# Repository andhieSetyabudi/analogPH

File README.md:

# analogPH
analogPH is a library to access my pH-board. Arduino compatibility. My pH using ADC-I2C ( ADS1112 ) for the main ADC-chip.

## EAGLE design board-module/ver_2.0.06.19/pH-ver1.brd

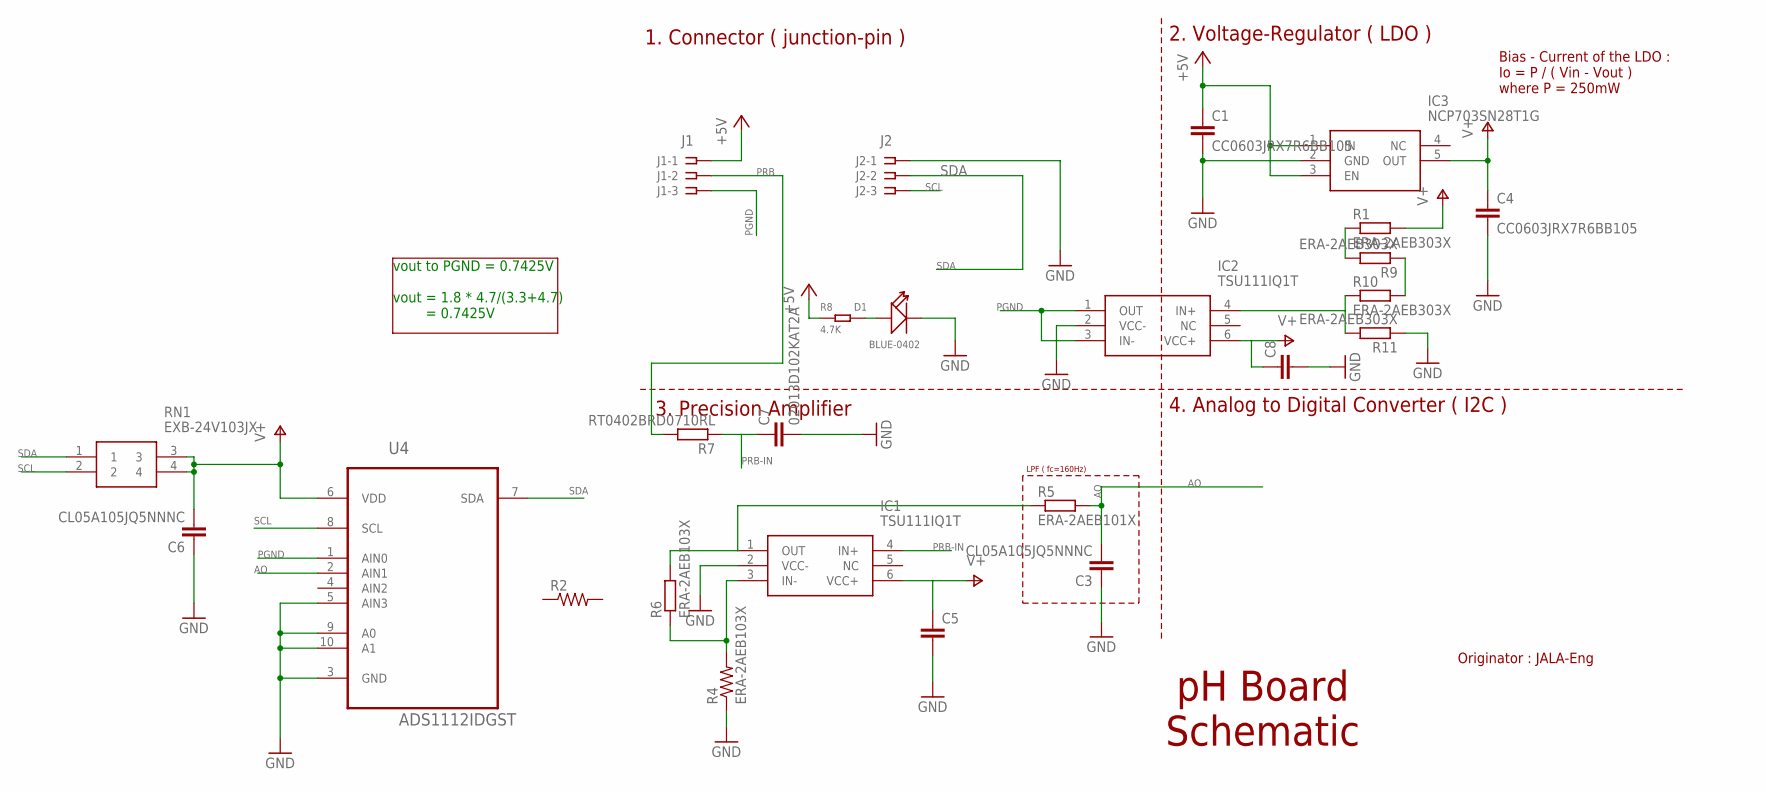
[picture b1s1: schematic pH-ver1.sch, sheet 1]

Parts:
C1, C4: CC0603JRX7R6BB105; C0603
C3, C6: CL05A105JQ5NNNC; C0402
C5, C8: C-EUC0402; C0402
C7: 02013D102KAT2A; C0402
D1: BLUE-0402; LED-0402
IC1, IC2: TSU111IQ1T
IC3: NCP703SN28T1G; SOT95P275X110-5N
J1: J1; SSW-103-02-S-S
J2: J2; SSW-103-02-S-S
R1, R9, R10, R11: ERA-2AEB303X; R0402
R2: R-US_R0201; R0201
R4: ERA-2AEB103X; R0201
R5: ERA-2AEB101X; R0402
R6: ERA-2AEB103X; R0402
R7: RT0402BRD0710RL; R0402
R8: 4.7K; R0402
RN1: EXB-24V103JX; EXB24V102JX
U4: ADS1112IDGST; SOP50P490X110-10N

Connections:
+5V: C1.1, IC3.1 (IN), IC3.3 (EN), J1.1, R8.1
AO: C3.2, R5.2, U4.2 (AIN1)
GND: C1.2, C3.1, C4.2, C5.2, C6.1, C7.2, C8.2, D1.-, IC1.2 (VCC-), IC2.2 (VCC-), IC3.2 (GND), J2.1, R4.1, R11.1, U4.3 (GND), U4.5 (AIN3), U4.9 (A0), U4.10 (A1)
unnamed: IC1.1 (OUT), R5.1, R6.2
unnamed: R1.1, R9.2
unnamed: R9.1, R10.2
unnamed: IC2.4 (IN+), R10.1, R11.2
unnamed: D1.+, R8.2
unnamed: IC1.3 (IN-), R4.2, R6.1
PGND: IC2.1 (OUT), IC2.3 (IN-), J1.3, U4.1 (AIN0)
PRB: J1.2, R7.2
PRB-IN: C7.1, IC1.4 (IN+), R7.1
SCL: J2.3, RN1.2, U4.8 (SCL)
SDA: J2.2, RN1.1, U4.7 (SDA)
V+: C4.1, C5.1, C6.2, C8.1, IC1.6 (VCC+), IC2.6 (VCC+), IC3.5 (OUT), R1.2, RN1.3, RN1.4, U4.6 (VDD)

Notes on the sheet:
Originator : JALA-Eng
pH Board Schematic
1. Connector ( junction-pin )
2. Voltage-Regulator ( LDO )
3. Precision Amplifier
4. Analog to Digital Converter ( I2C )
LPF ( fc=160Hz)
Bias - Current of the LDO : Io = P / ( Vin - Vout ) where P = 250mW
vout to PGND = 0.7425V vout = 1.8 * 4.7/(3.3+4.7) = 0.7425V

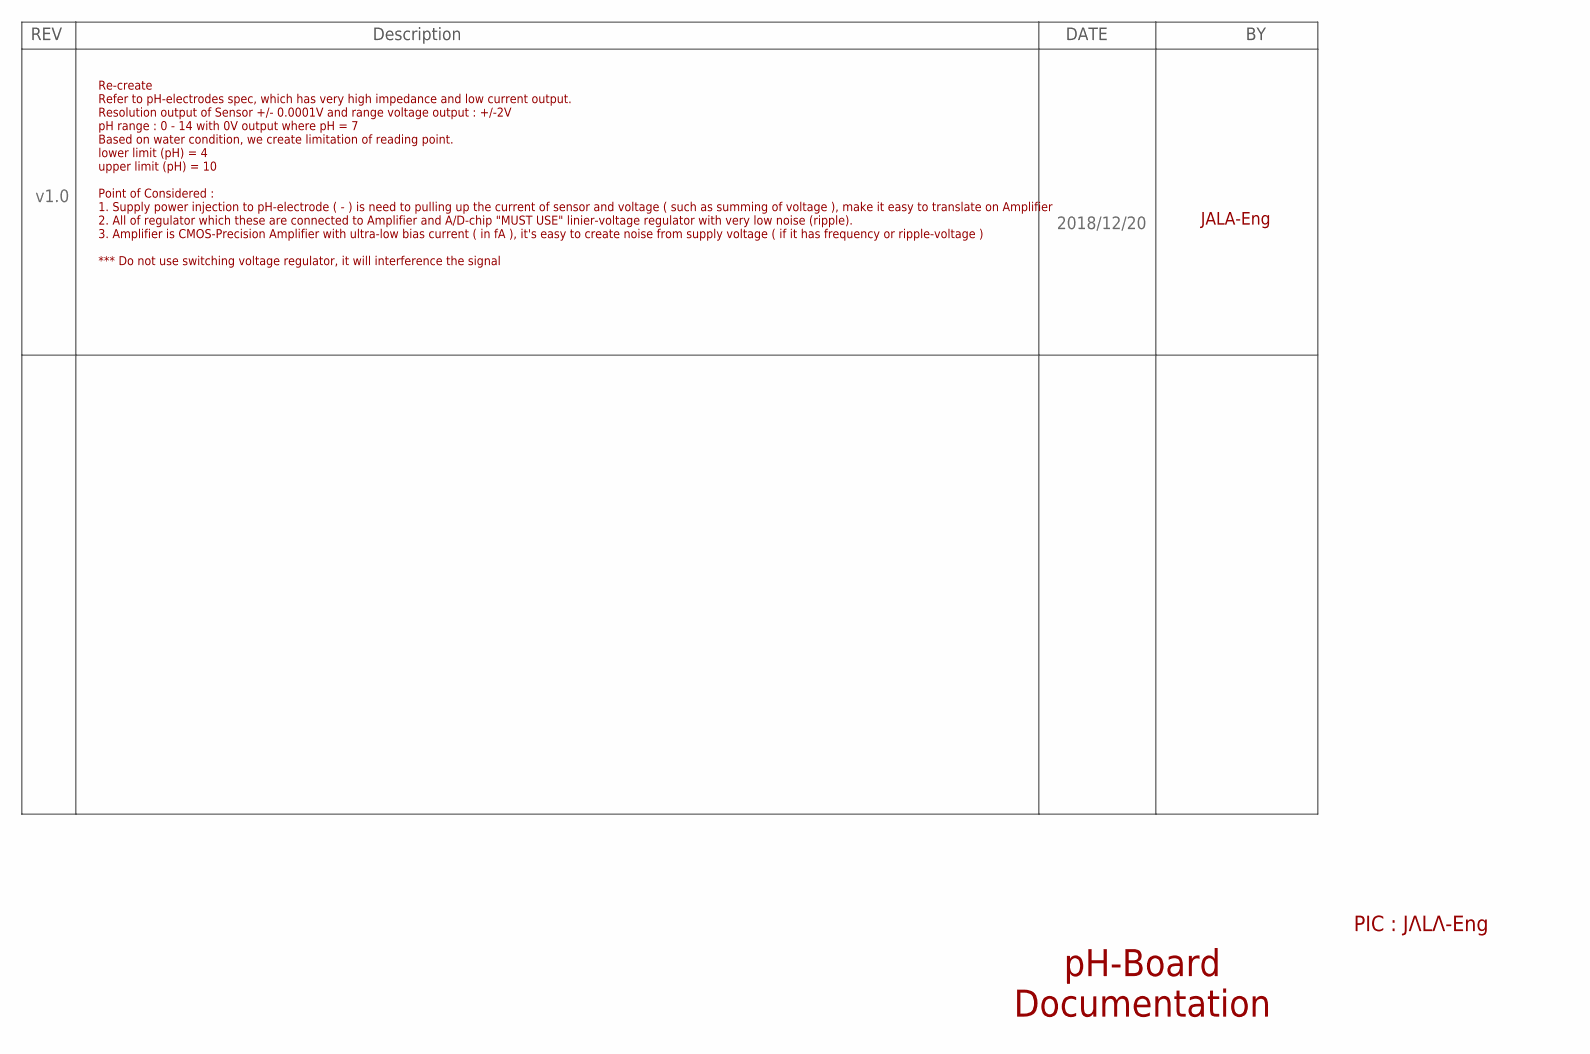
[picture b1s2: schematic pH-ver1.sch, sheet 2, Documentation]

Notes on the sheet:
PIC : JΛLΛ-Eng
pH-Board Documentation
v1.0
2018/12/20
Re-create Refer to pH-electrodes spec, which has very high impedance and low current output. Resolution output of Sensor +/- 0.0001V and range voltage output : +/-2V pH range : 0 - 14 with 0V output where pH = 7 Based on water condition, we create limitation of reading point. lower limit (pH) = 4 u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
JALA-Eng

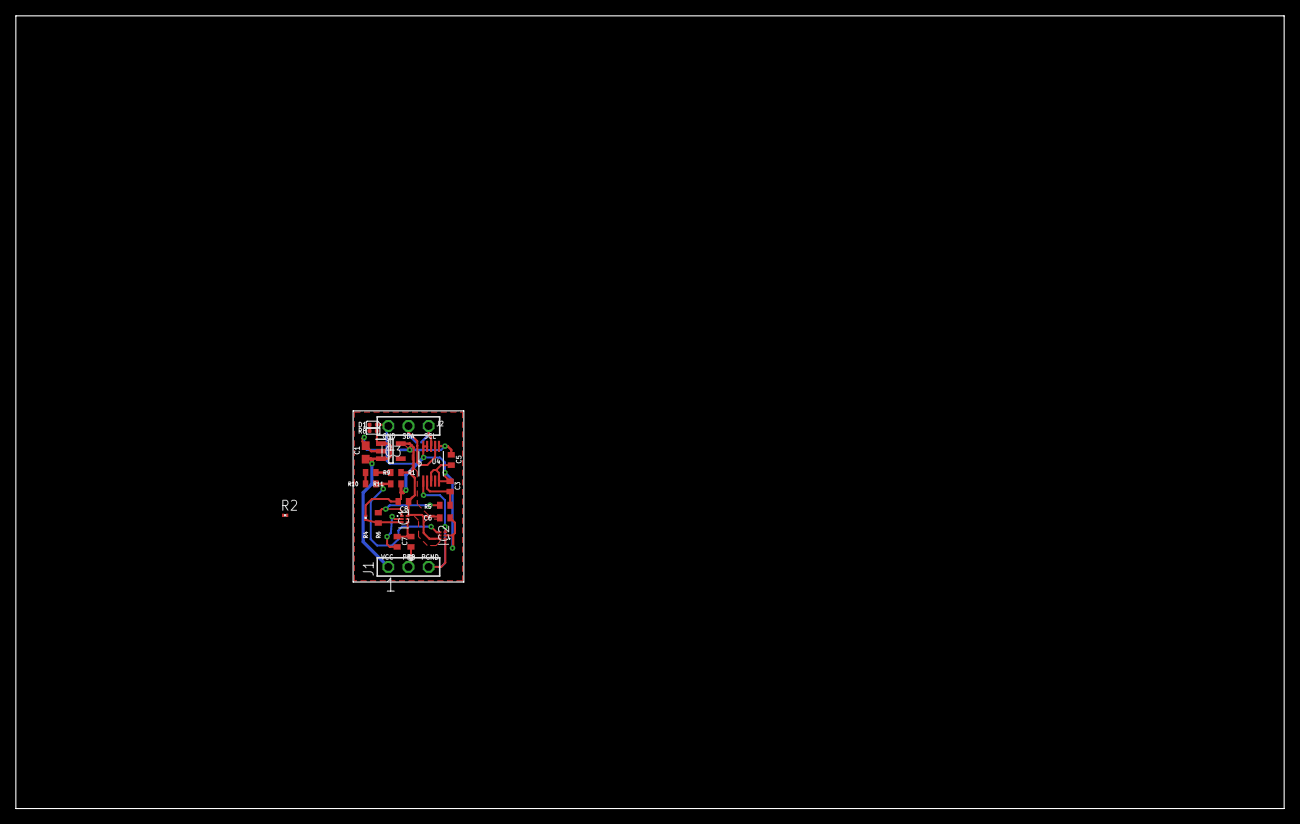
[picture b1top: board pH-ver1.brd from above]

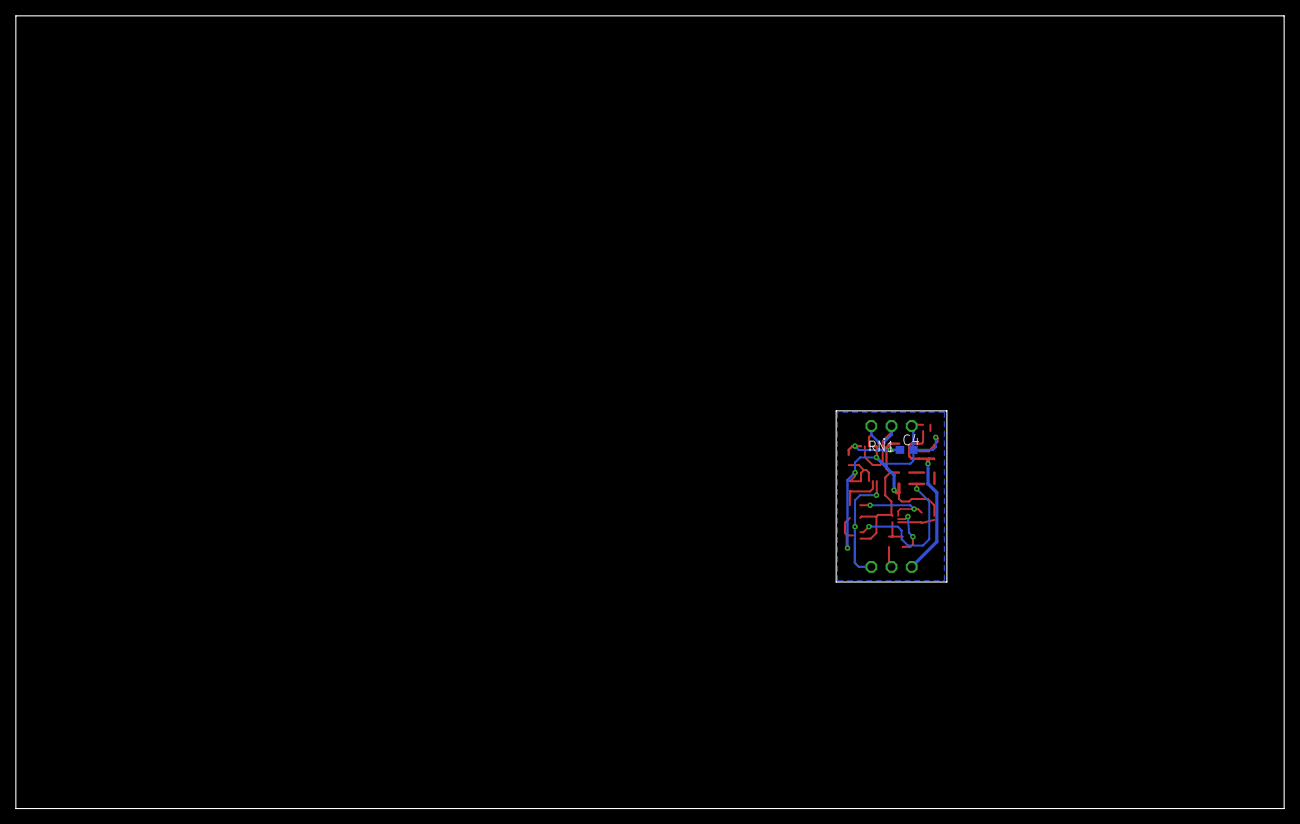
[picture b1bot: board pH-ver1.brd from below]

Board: 2 copper layers, 160.0 x 100.0 mm, 25 parts (2 on the bottom side), 15 nets.
